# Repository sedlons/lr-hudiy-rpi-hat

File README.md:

## lr-hudiy-rpi-hat
RPi hat suitable for HUDIY. I used it in Land Rover Discovery II.

Functions:
 - self power control with latch-up
 - steering wheel resistance button read
 - power control of RPi
 - rotary encoder (volume)
 - light sensor (control backlight/da/night mode)
 - heater power on by timing with RTC (NOT IMPLEMENTED IN HUDIY YET)
 - webasto RX/TX interface (NOT TESTED YET)
 - connector for I2C gyroscope for inclinometer (NOT IMPLEMENTED IN HUDIY YET)

Python code is used for communicating between HUDIY and arduino.

Old project name was lr-openauto-hat, because first version was used with OpenAuto.

## License

This project is licensed under the [GNU GPLv3](https://www.gnu.org/licenses/gpl-3.0.html).

- ✅ The code can be freely used, distributed, and modified.  
- 🔄 All modifications must be released under the same license.  
- ⚠️ This license does **not** prohibit commercial use.

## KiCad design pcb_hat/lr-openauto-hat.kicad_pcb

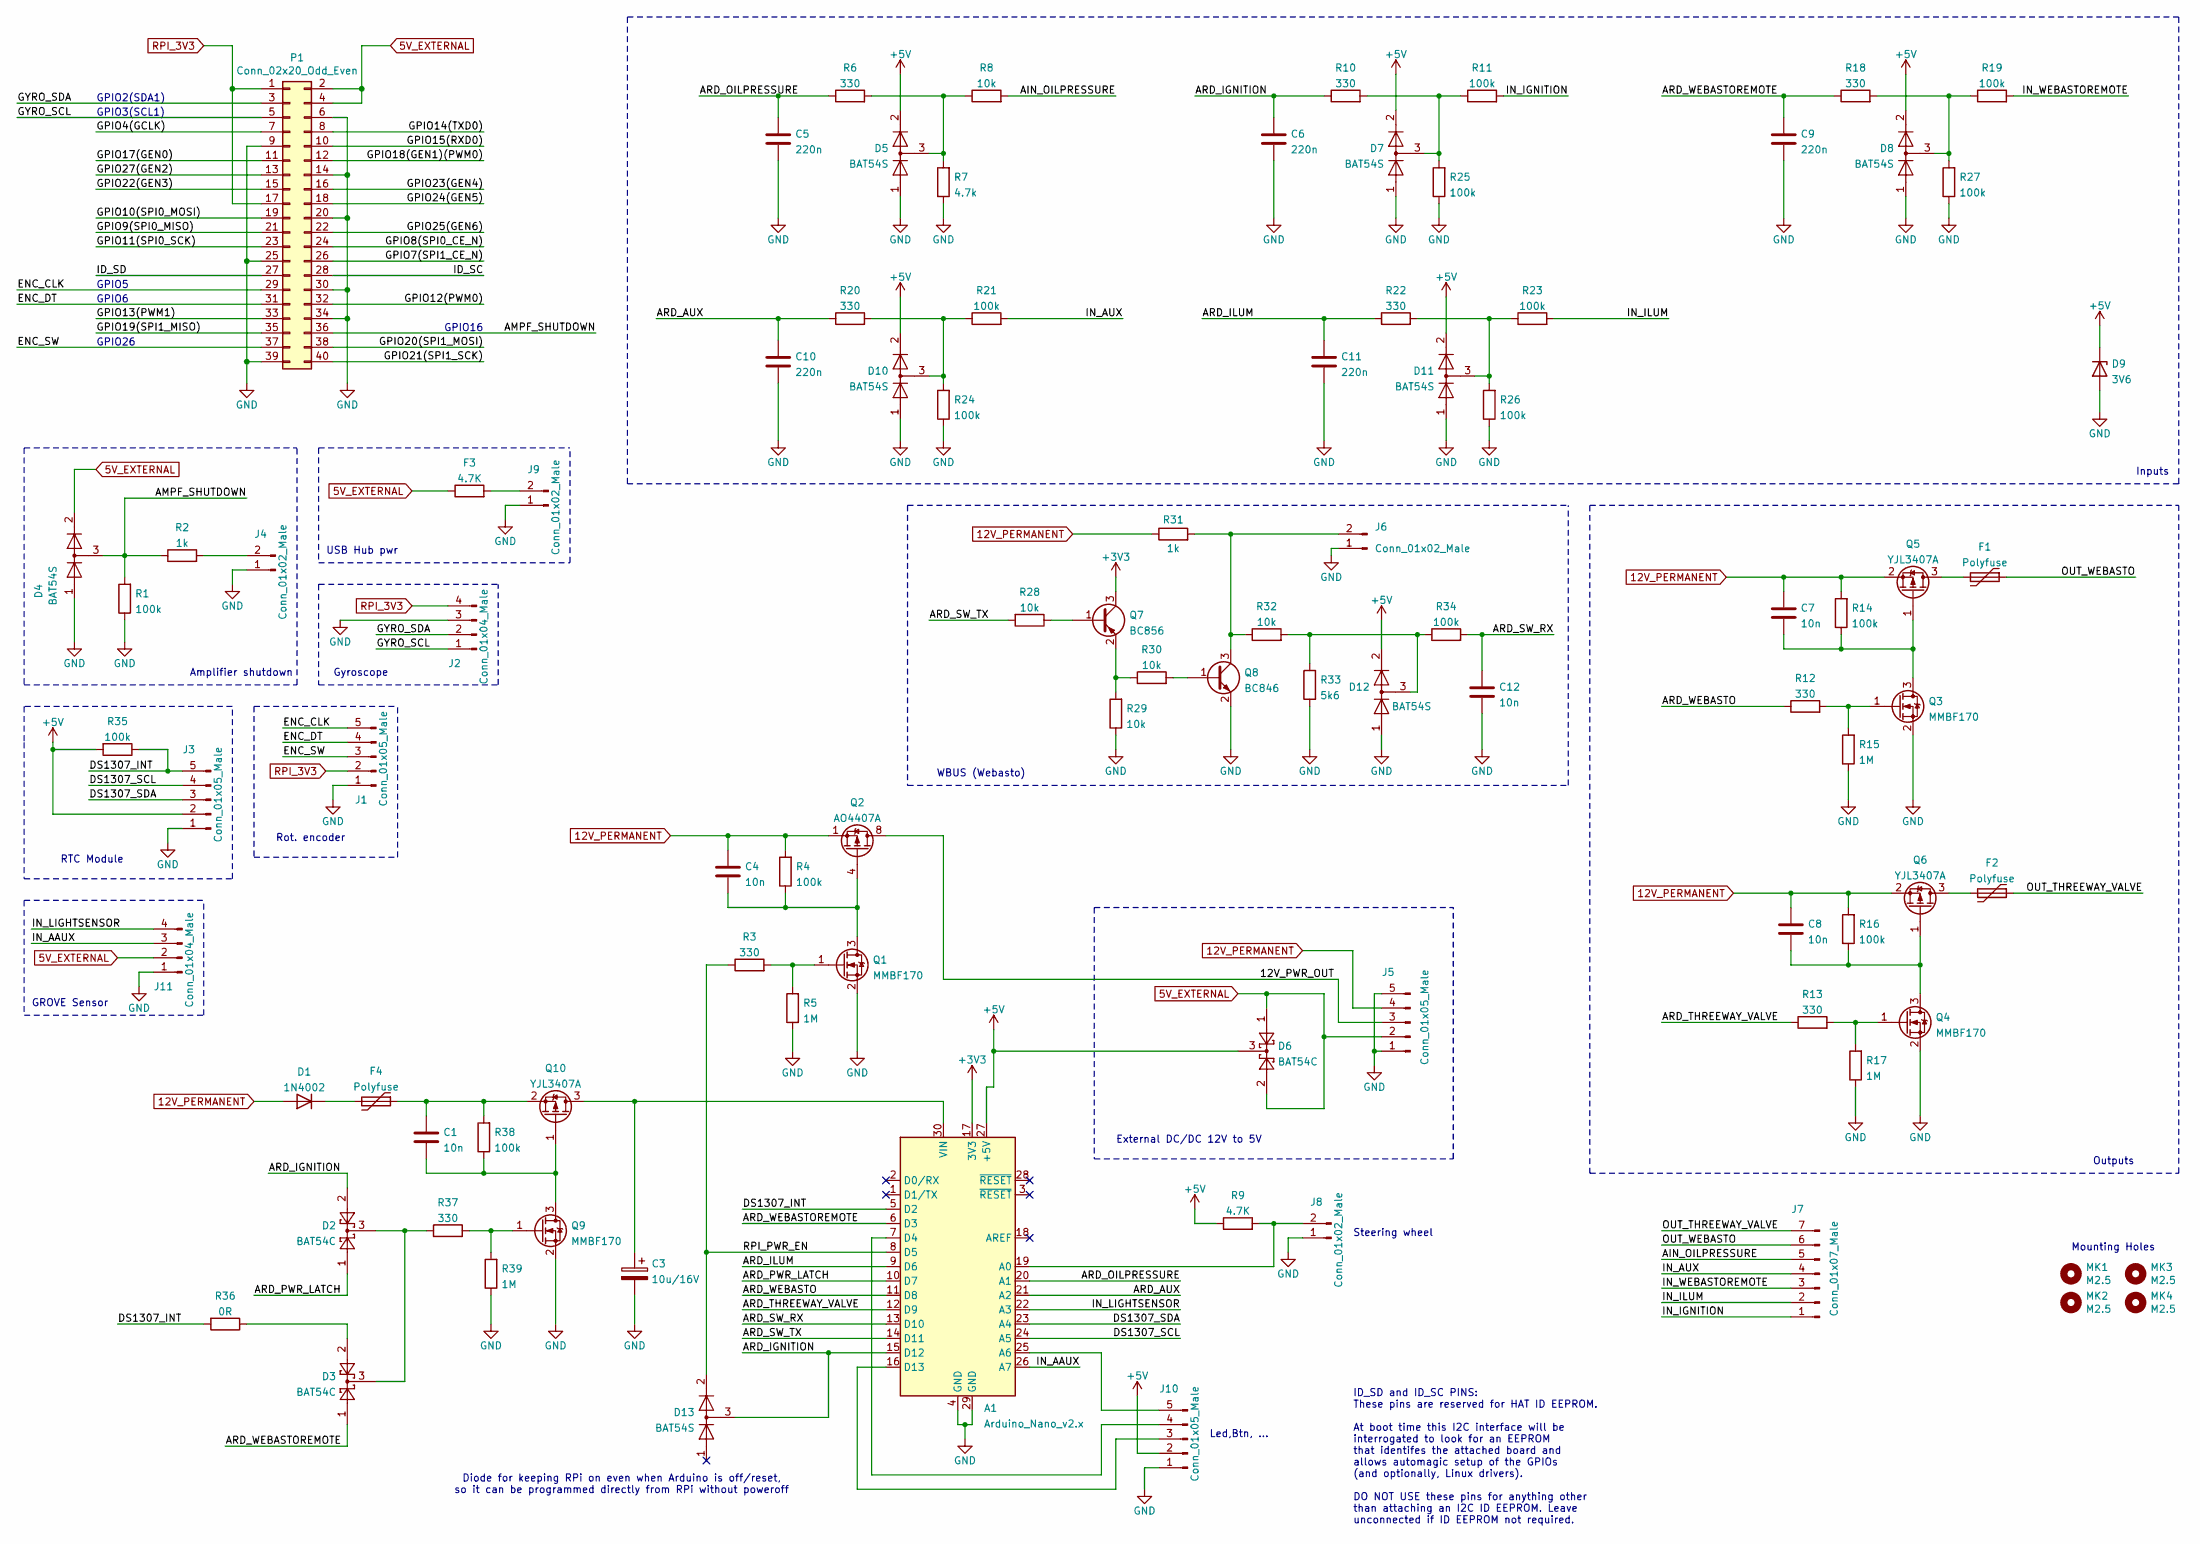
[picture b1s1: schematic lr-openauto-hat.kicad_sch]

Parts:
A1: Arduino_Nano_v2.x; Arduino_Nano
C1, C4, C7, C8, C12: 10n; C_0805_2012Metric
C3: 10u/16V; CP_Radial_D5.0mm_P2.50mm
C5, C6, C9, C10, C11: 220n; C_0805_2012Metric
D1: 1N4002; D_DO-41_SOD81_P2.54mm_Vertical_AnodeUp
D2, D3, D6: BAT54C; SOT-23
D4, D5, D7, D8, D10, D11, D12, D13: BAT54S; SOT-23
D9: 3V6; D_DO-41_SOD81_P2.54mm_Vertical_AnodeUp
F1, F2, F4: Polyfuse; Fuse_0805_2012Metric_Pad1.15x1.40mm_HandSolder
F3: 4.7K; R_0805_2012Metric_Pad1.20x1.40mm_HandSolder
J1, J3, J10: Conn_01x05_Male; JST_PH_B5B-PH-K_1x05_P2.00mm_Vertical
J2, J11: Conn_01x04_Male; JST_PH_B4B-PH-K_1x04_P2.00mm_Vertical
J4, J6, J8, J9: Conn_01x02_Male; JST_PH_B2B-PH-K_1x02_P2.00mm_Vertical
J5: Conn_01x05_Male; Molex_Micro-Fit_3.0_43650-0515_1x05_P3.00mm_Vertical
J7: Conn_01x07_Male; Molex_Micro-Fit_3.0_43650-0715_1x07_P3.00mm_Vertical
MK1, MK2, MK3, MK4: M2.5; MountingHole_2.7mm_M2.5
P1: Conn_02x20_Odd_Even; PinSocket_2x20_P2.54mm_Vertical
Q1, Q3, Q4, Q9: MMBF170; SOT-23
Q2: AO4407A; SOIC-8_3.9x4.9mm_P1.27mm
Q5, Q6, Q10: YJL3407A; SOT-23
Q7: BC856; SOT-23
Q8: BC846; SOT-23
R1, R4, R11, R14, R16, R19, R21, R23, R24, R25, R26, R27, R34, R35, R38: 100k; R_0805_2012Metric
R2, R31: 1k; R_0805_2012Metric
R3, R6, R10, R12, R13, R18, R20, R22, R37: 330; R_0805_2012Metric
R5, R15, R17, R39: 1M; R_0805_2012Metric
R7: 4.7k; R_0805_2012Metric
R8, R28, R29, R30, R32: 10k; R_0805_2012Metric
R9: 4.7K; R_0805_2012Metric
R33: 5k6; R_0805_2012Metric
R36: 0R; R_0805_2012Metric

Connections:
5V_EXTERNAL: D4.2 (A), D6.1, D6.2, F3.1, J5.2, J11.2, P1.2, P1.4
12V_PERMANENT: C4.1, C7.1, C8.1, D1.2 (A), J5.4, Q2.1 (S), Q2.2 (S), Q2.3 (S), Q5.2 (S), Q6.2 (S), R4.2, R14.2, R16.2, R31.1
+3V3: A1.17 (3V3), Q7.3 (C)
+5V: A1.27 (+5V), D5.2 (A), D6.3, D7.2 (A), D8.2 (A), D9.1 (K), D10.2 (A), D11.2 (A), D12.2 (A), J3.2, J10.2, R9.1, R35.2
/12V_PWR_OUT: J5.3, Q2.5 (D), Q2.6 (D), Q2.7 (D), Q2.8 (D)
/AIN_OILPRESSURE: J7.5, R8.2
/AMPF_SHUTDOWN: D4.3 (K), P1.36, R1.2, R2.1
/ARD_AUX: A1.21 (A2), C10.1, R20.1
/ARD_IGNITION: A1.15 (D12), C6.1, D2.2, D13.3 (K), R10.1
/ARD_ILUM: A1.9 (D6), C11.1, R22.1
/ARD_OILPRESSURE: A1.20 (A1), C5.1, R6.1
/ARD_PWR_LATCH: A1.10 (D7), D2.1
/ARD_SW_RX: A1.13 (D10), C12.1, R34.2
/ARD_SW_TX: A1.14 (D11), R28.2
/ARD_THREEWAY_VALVE: A1.12 (D9), R13.1
/ARD_WEBASTO: A1.11 (D8), R12.1
/ARD_WEBASTOREMOTE: A1.6 (D3), C9.1, D3.1, R18.1
/DS1307_INT: A1.5 (D2), J3.5, R35.1, R36.2
/DS1307_SCL: A1.24 (A5), J3.4
/DS1307_SDA: A1.23 (A4), J3.3
/ENC_CLK: J1.5, P1.29
/ENC_DT: J1.4, P1.31
/ENC_SW: J1.3, P1.37
/GPIO4(GCLK): P1.7
/GPIO7(SPI1_CE_N): P1.26
/GPIO8(SPI0_CE_N): P1.24
/GPIO9(SPI0_MISO): P1.21
/GPIO10(SPI0_MOSI): P1.19
/GPIO11(SPI0_SCK): P1.23
/GPIO12(PWM0): P1.32
/GPIO13(PWM1): P1.33
/GPIO14(TXD0): P1.8
/GPIO15(RXD0): P1.10
/GPIO17(GEN0): P1.11
/GPIO18(GEN1)(PWM0): P1.12
/GPIO19(SPI1_MISO): P1.35
/GPIO20(SPI1_MOSI): P1.38
/GPIO21(SPI1_SCK): P1.40
/GPIO22(GEN3): P1.15
/GPIO23(GEN4): P1.16
/GPIO24(GEN5): P1.18
/GPIO25(GEN6): P1.22
/GPIO27(GEN2): P1.13
/GYRO_SCL: J2.1, P1.5
/GYRO_SDA: J2.2, P1.3
/ID_SC: P1.28
/ID_SD: P1.27
/IN_AAUX: A1.26 (A7), J11.3
/IN_AUX: J7.4, R21.2
/IN_IGNITION: J7.1, R11.2
/IN_ILUM: J7.2, R23.2
/IN_LIGHTSENSOR: A1.22 (A3), J11.4
/IN_WEBASTOREMOTE: J7.3, R19.2
/OUT_THREEWAY_VALVE: F2.1, J7.7
/OUT_WEBASTO: F1.1, J7.6
/RPI_PWR_EN: A1.8 (D5), D13.2 (A), R3.1
GND: A1.4 (GND), A1.29 (GND), C3.2, C5.2, C6.2, C9.2, C10.2, C11.2, C12.2, D4.1 (K), D5.1 (K), D7.1 (K), D8.1 (K), D9.2 (A), D10.1 (K), D11.1 (K), D12.1 (K), J1.1, J2.3, J3.1, J4.1, J5.1, J5.5, J6.1, J8.1, J9.1, J10.1, J11.1, P1.6, P1.9, P1.14, P1.20, P1.25, P1.30, P1.34, P1.39, Q1.2 (S), Q3.2 (S), Q4.2 (S), Q8.2 (E), Q9.2 (S), R1.1, R5.1, R7.1, R15.1, R17.1, R24.1, R25.1, R26.1, R27.1, R29.1, R33.2, R39.1
unnamed: A1.19 (A0), J8.2, R9.2
unnamed: A1.25 (A6), J10.5
unnamed: A1.7 (D4), J10.4
unnamed: A1.16 (D13), J10.3
unnamed: A1.30 (VIN), C3.1, Q10.3 (D)
unnamed: D1.1 (K), F4.2
unnamed: D2.3, D3.3, R37.1
unnamed: D3.2, R36.1
unnamed: D5.3 (K), R6.2, R7.2, R8.1
unnamed: D7.3 (K), R10.2, R11.1, R25.2
unnamed: D8.3 (K), R18.2, R19.1, R27.2
unnamed: D10.3 (K), R20.2, R21.1, R24.2
unnamed: D11.3 (K), R22.2, R23.1, R26.2
unnamed: D12.3 (K), R32.2, R33.1, R34.1
unnamed: J4.2, R2.2
unnamed: J6.2, Q8.3 (C), R31.2, R32.1
unnamed: F3.2, J9.2
unnamed: C4.2, Q1.3 (D), Q2.4 (G), R4.1
unnamed: Q1.1 (G), R3.2, R5.2
unnamed: C7.2, Q3.3 (D), Q5.1 (G), R14.1
unnamed: Q3.1 (G), R12.2, R15.2
unnamed: C8.2, Q4.3 (D), Q6.1 (G), R16.1
unnamed: Q4.1 (G), R13.2, R17.2
unnamed: F1.2, Q5.3 (D)
unnamed: F2.2, Q6.3 (D)
unnamed: Q7.1 (B), R28.1
unnamed: Q7.2 (E), R29.2, R30.1
unnamed: Q8.1 (B), R30.2
unnamed: Q9.1 (G), R37.2, R39.2
unnamed: C1.2, Q9.3 (D), Q10.1 (G), R38.1
unnamed: C1.1, F4.1, Q10.2 (S), R38.2
RPI_3V3: J1.2, J2.4, P1.1, P1.17

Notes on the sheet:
RTC Module
GROVE Sensor
ID_SD and ID_SC PINS: These pins are reserved for HAT ID EEPROM. At boot time this I2C interface will be interrogated to look for an EEPROM that identifes the attached board and allows automagic setup of the GPIOs (and optionally, Linux drivers). DO NOT USE these pins for anything other than attach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
GPIO5
Outputs
Gyroscope
Amplifier shutdown
GPIO26
Led,Btn, ...
External DC/DC 12V to 5V
GPIO3(SCL1)
Steering wheel
GPIO6
Mounting Holes
Diode for keeping RPi on even when Arduino is off/reset, so it can be programmed directly from RPi without poweroff
USB Hub pwr
GPIO2(SDA1)
Inputs
WBUS (Webasto)
Rot. encoder
GPIO16

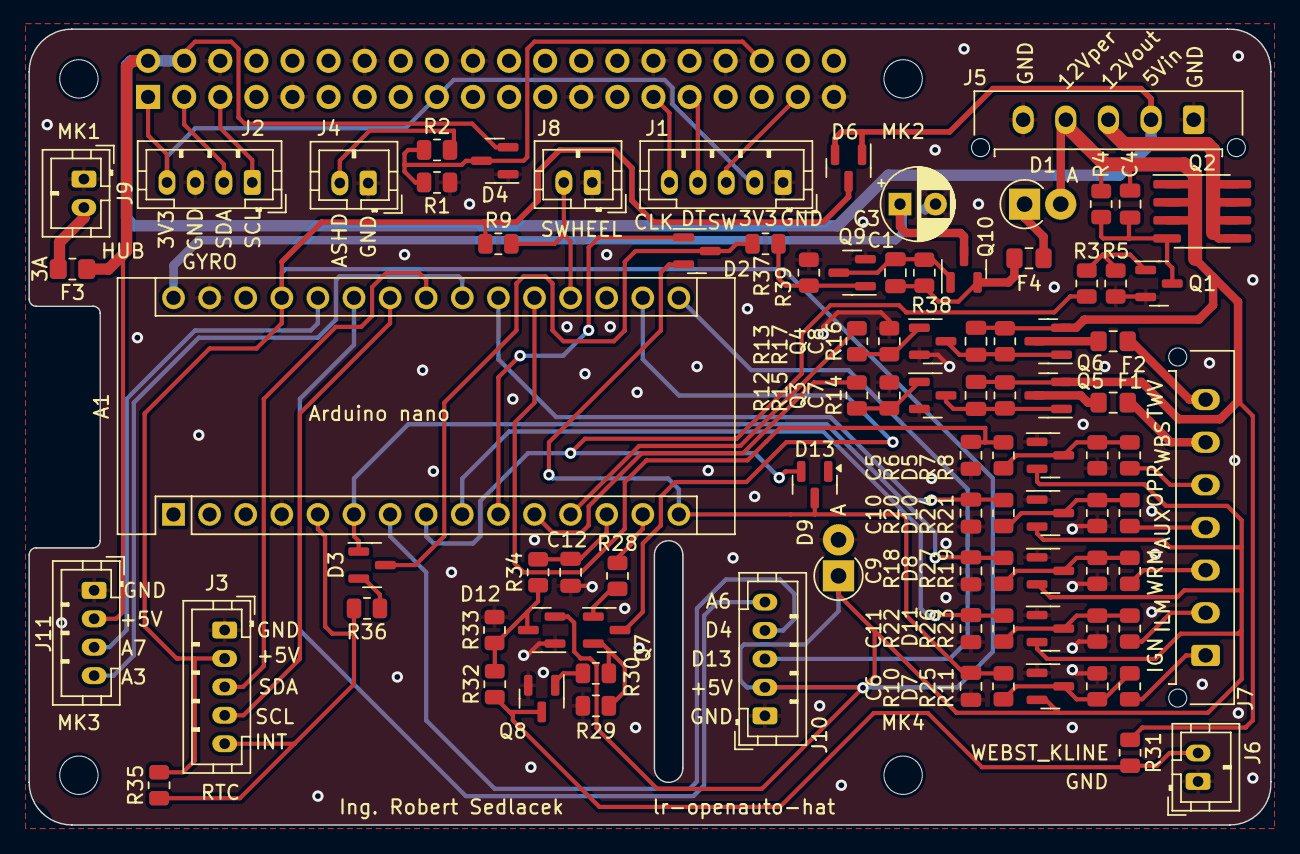
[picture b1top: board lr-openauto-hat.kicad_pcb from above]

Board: 2 copper layers, 87.4 x 56.0 mm, 94 parts (1 on the bottom side), 67 nets.

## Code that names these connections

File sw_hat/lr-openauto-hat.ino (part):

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
/* Input/output/analog pin definitions */
#define PIN_D4           4  /* */
#define PIN_RPI_PWR_EN   5  /* output-enable rpi power */
#define PIN_ILUM         6  /* */
#define PIN_PWR_LATCH    7  /* output-latching power */
#define PIN_WEBASTO      8  /* */
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#define PIN_OIL_PRESS    A1 /* */
#define PIN_AUX          A2 /* */
#define PIN_LIGHT_SENS   A3 /* */
#define PIN_DS1307_SDA   A4 /* */
#define PIN_DS1307_SCL   A5 /* */
#define PIN_A6           A6 /* */
#define PIN_AAUX         A7 /* */

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  memset(&state, 0, sizeof(state));

  /* Configure outputs */
  pinMode(PIN_RPI_PWR_EN, INPUT);
  //digitalWrite(PIN_RPI_PWR_EN, HIGH);
  
  pinMode(PIN_THR_VALVE, OUTPUT);
  digitalWrite(PIN_THR_VALVE, LOW);
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  if(state.in.ignition != HIGH && state.out.rpi_pwr_en != LOW) {
    if(millis() - state.timestamps.last_ignition_change > (unsigned long)settings.shutdown_delay_rpi*1000ul) {
      Serial.println("RPi power OFF");
      pinMode(PIN_RPI_PWR_EN, OUTPUT);
      //state.out.rpi_pwr_en = LOW;
      delay(150);
      pinMode(PIN_RPI_PWR_EN, INPUT);
    }
  }  
}
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/* Writing outputs, serial outputs, etc. */
/*------------------------------------------------------------------------------------------------------*/
void output_write(void) {
  digitalWrite(PIN_RPI_PWR_EN, state.out.rpi_pwr_en);
}

/*------------------------------------------------------------------------------------------------------*/
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
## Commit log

2024-12-30 Prvni commit
2024-12-30 Ovladani webasta
2025-08-24 Transition from openauto to hudiy
2025-08-24 Pridana licence a zmena nazvu
2025-11-30 encoder-volume modification for pipewire
2025-12-02 First version of inclinometer plugin
2025-12-02 Added video
2025-12-02 Better video thumb
